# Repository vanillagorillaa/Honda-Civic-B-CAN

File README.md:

Honda B-CAN Integration
====

Get your panda deeper into your 2016+ Honda Civic, may work on other cars too, check Honda Techinfo for more details.

The Idea  
====

Access data found on a third CAN bus on your Honda Vehicle. Data on this bus includes Blind Spot Indicators (if vehicle equipped), lights, climate controls, and more.

Installation
====

This is a two part setup.

- Gateway - The Gateway contains a comma.ai panda [https://github.com/commaai/panda]. It has three CAN busses and uses the panda firmware to proxy the CAN messages from one bus to the other. Currently we are taking all messages from the BCAN (150kbps) and forwarding them onto the FCAN (500kbps). This will allow devices such as the comma two [https://comma.ai/shop/products/comma-two-devkit] and openpilot [https://github.com/commaai/openpilot] to see these new messages, and in the future, control. The gateway has six ethernet ports. Each ethernet port is labeled with its functionality as each is wired differently (see schematic for wiring). The gateway also has 0402 pads for terminating resistors on each bus (if needed). The Gateway is designed to be agnostic to vehicles. Simply follow the wiring to make your own compatible "Car Specific Board". Also includes a USB A for flashing the panda. 

1x - To Harness
1x - To OBDII Port/ comma power
1x - To pedal
2x - Car Specific board
1x - Expansion

- Honda B-CAN - This board has two JAE MX34036NF4 connectors and one Ethernet port. It is designed to connect to the 36 pin connector on the BCM of select Honda vehicles. The install procedure is so unplug the wiring harness from the BCM (confirmed on 2016 Honda Civic and 2017 Honda CRV, for more vehicles check Techinfo), connect it to the B-CAN board, then use the additional wiring harness (MX34036SF4 to MX34036SF4) to install between the B-CAN board and the BCM. Then use an ethernet cable to connect to the Gateway. This allows a full passthrough of the BCM harness, and taps into the BCAN and FCAN lines (to the Ethernet port). You can also sub the above JAE part numbers for another MX34036 series connector (just be sure to trim the connectors as seen in the build guide, otherwise the connector will not fit in the BCM)

====

Contributions welcome! Documentation can be greatly improved! Make a more detailed build guide!

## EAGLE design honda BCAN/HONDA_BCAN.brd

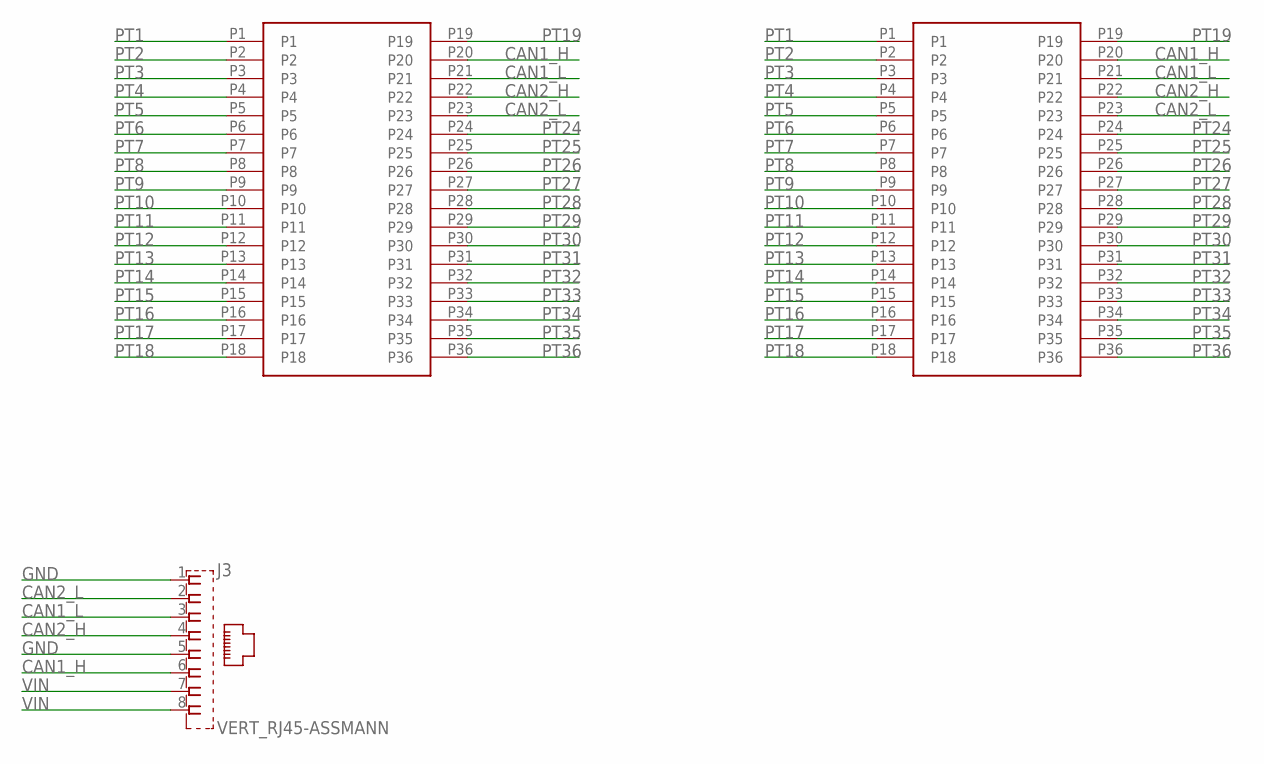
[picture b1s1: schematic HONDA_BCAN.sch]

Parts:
J1, J2: MX34036NF4; MPN MX34036NF4
J3: VERT_RJ45-ASSMANN; RJ45-VERT; MPN A-2004-2-4-LPS-N-R

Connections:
CAN1_H: J1.P20, J2.P20, J3.6
CAN1_L: J1.P21, J2.P21, J3.3
CAN2_H: J1.P22, J2.P22, J3.4
CAN2_L: J1.P23, J2.P23, J3.2
GND: J3.1, J3.5
PT1: J1.P1, J2.P1
PT2: J1.P2, J2.P2
PT3: J1.P3, J2.P3
PT4: J1.P4, J2.P4
PT5: J1.P5, J2.P5
PT6: J1.P6, J2.P6
PT7: J1.P7, J2.P7
PT8: J1.P8, J2.P8
PT9: J1.P9, J2.P9
PT10: J1.P10, J2.P10
PT11: J1.P11, J2.P11
PT12: J1.P12, J2.P12
PT13: J1.P13, J2.P13
PT14: J1.P14, J2.P14
PT15: J1.P15, J2.P15
PT16: J1.P16, J2.P16
PT17: J1.P17, J2.P17
PT18: J1.P18, J2.P18
PT19: J1.P19, J2.P19
PT24: J1.P24, J2.P24
PT25: J1.P25, J2.P25
PT26: J1.P26, J2.P26
PT27: J1.P27, J2.P27
PT28: J1.P28, J2.P28
PT29: J1.P29, J2.P29
PT30: J1.P30, J2.P30
PT31: J1.P31, J2.P31
PT32: J1.P32, J2.P32
PT33: J1.P33, J2.P33
PT34: J1.P34, J2.P34
PT35: J1.P35, J2.P35
PT36: J1.P36, J2.P36
VIN: J3.7, J3.8

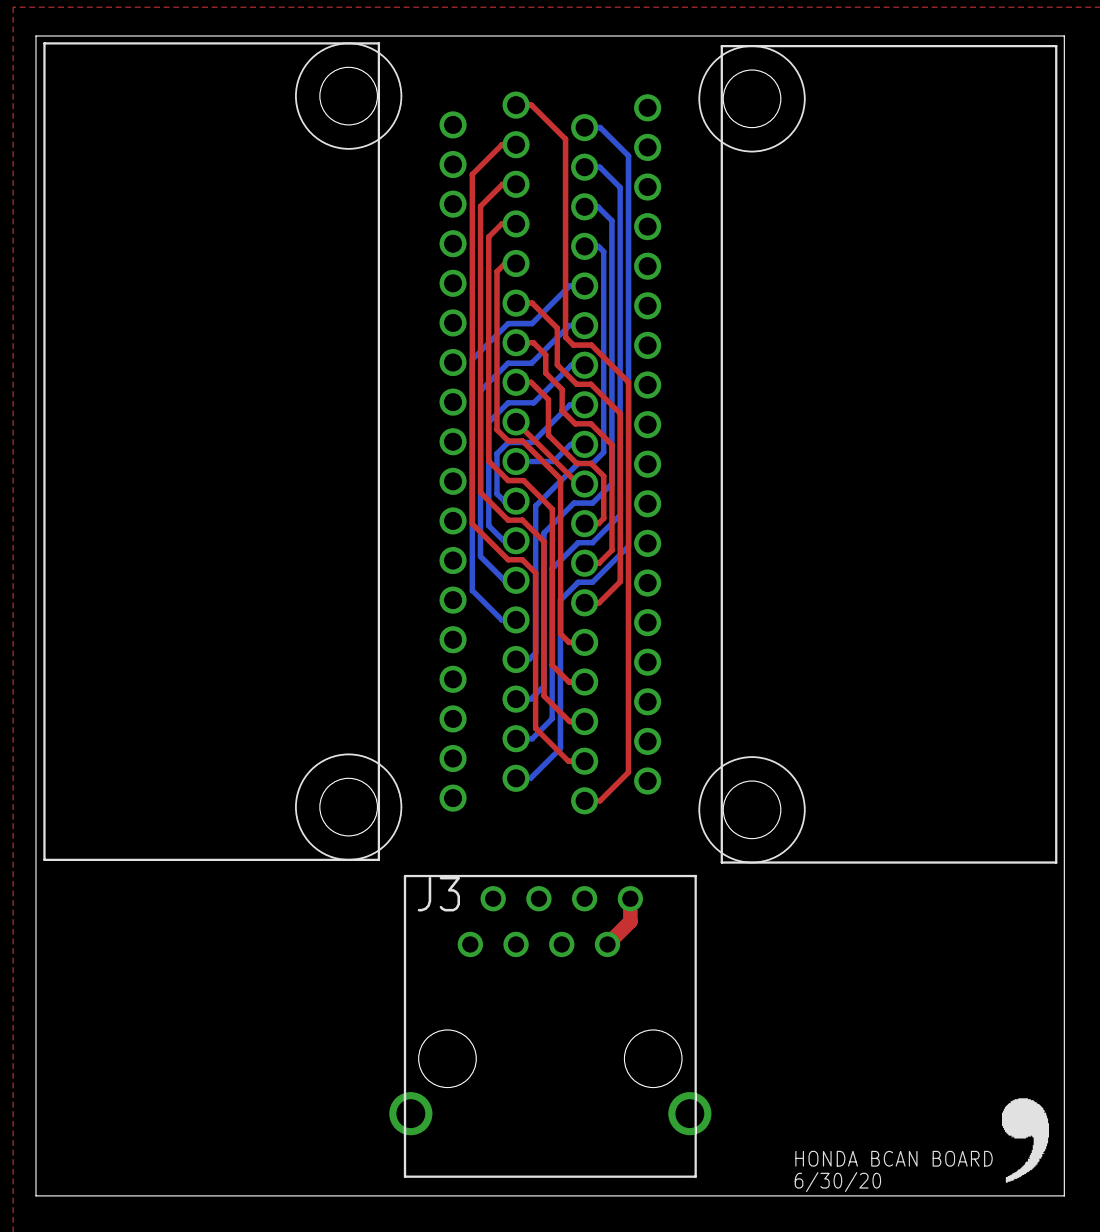
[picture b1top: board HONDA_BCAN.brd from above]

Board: 4 copper layers, 57.1 x 64.4 mm, 4 parts (0 on the bottom side), 38 nets.

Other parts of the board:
U$1: LOGO

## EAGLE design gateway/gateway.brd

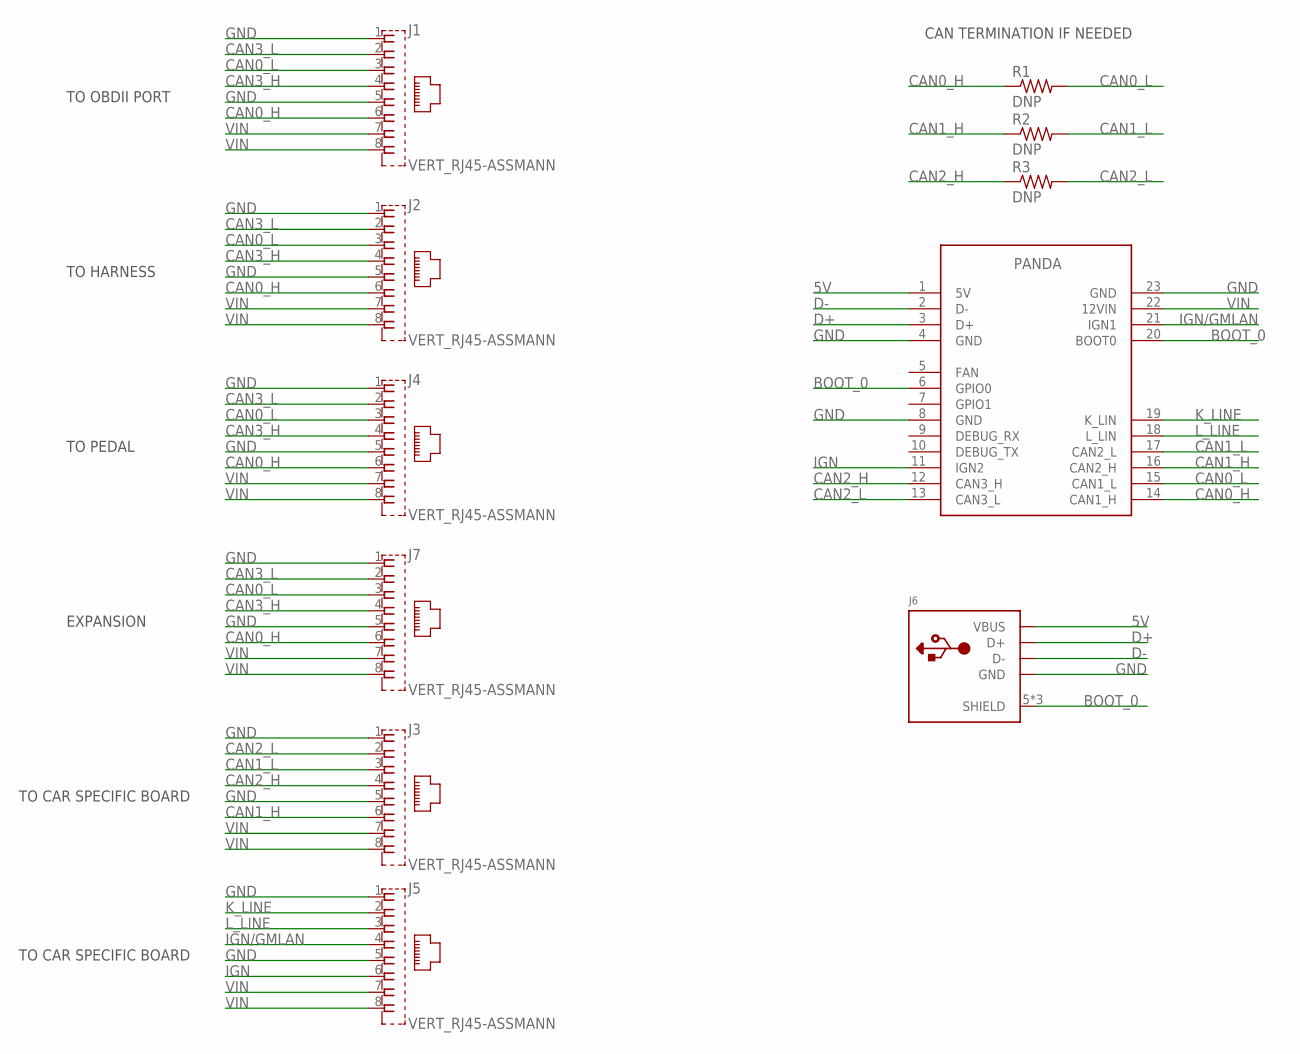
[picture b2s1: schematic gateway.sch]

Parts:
J1, J2, J3, J4, J5, J7: VERT_RJ45-ASSMANN; RJ45-VERT; MPN A-2004-2-4-LPS-N-R
J6: USB-AMOLEX; USB-A-VERT-MOLEX; MPN 1050570001
R1, R2, R3: DNP; 0603-R
U$1: PANDA; PANDA-FOOT

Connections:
5V: J6.1 (VBUS), U$1.1 (5V)
BOOT_0: J6.5 (SHIELD), J6.6 (SHIELD), J6.7 (SHIELD), U$1.6 (GPIO0), U$1.20 (BOOT0)
CAN0_H: J1.6, J2.6, J4.6, J7.6, R1.1, U$1.14 (CAN1_H)
CAN0_L: J1.3, J2.3, J4.3, J7.3, R1.2, U$1.15 (CAN1_L)
CAN1_H: J3.6, R2.1, U$1.16 (CAN2_H)
CAN1_L: J3.3, R2.2, U$1.17 (CAN2_L)
CAN2_H: J3.4, R3.1, U$1.12 (CAN3_H)
CAN2_L: J3.2, R3.2, U$1.13 (CAN3_L)
CAN3_H: J1.4, J2.4, J4.4, J7.4
CAN3_L: J1.2, J2.2, J4.2, J7.2
D+: J6.3 (D+), U$1.3 (D+)
D-: J6.2 (D-), U$1.2 (D-)
GND: J1.1, J1.5, J2.1, J2.5, J3.1, J3.5, J4.1, J4.5, J5.1, J5.5, J6.4 (GND), J7.1, J7.5, U$1.4 (GND), U$1.8 (GND), U$1.23 (GND)
IGN: J5.6, U$1.11 (IGN2)
IGN/GMLAN: J5.4, U$1.21 (IGN1)
K_LINE: J5.2, U$1.19 (K_LIN)
L_LINE: J5.3, U$1.18 (L_LIN)
VIN: J1.7, J1.8, J2.7, J2.8, J3.7, J3.8, J4.7, J4.8, J5.7, J5.8, J7.7, J7.8, U$1.22 (12VIN)

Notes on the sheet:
TO OBDII PORT
TO HARNESS
TO PEDAL
TO CAR SPECIFIC BOARD
EXPANSION
CAN TERMINATION IF NEEDED

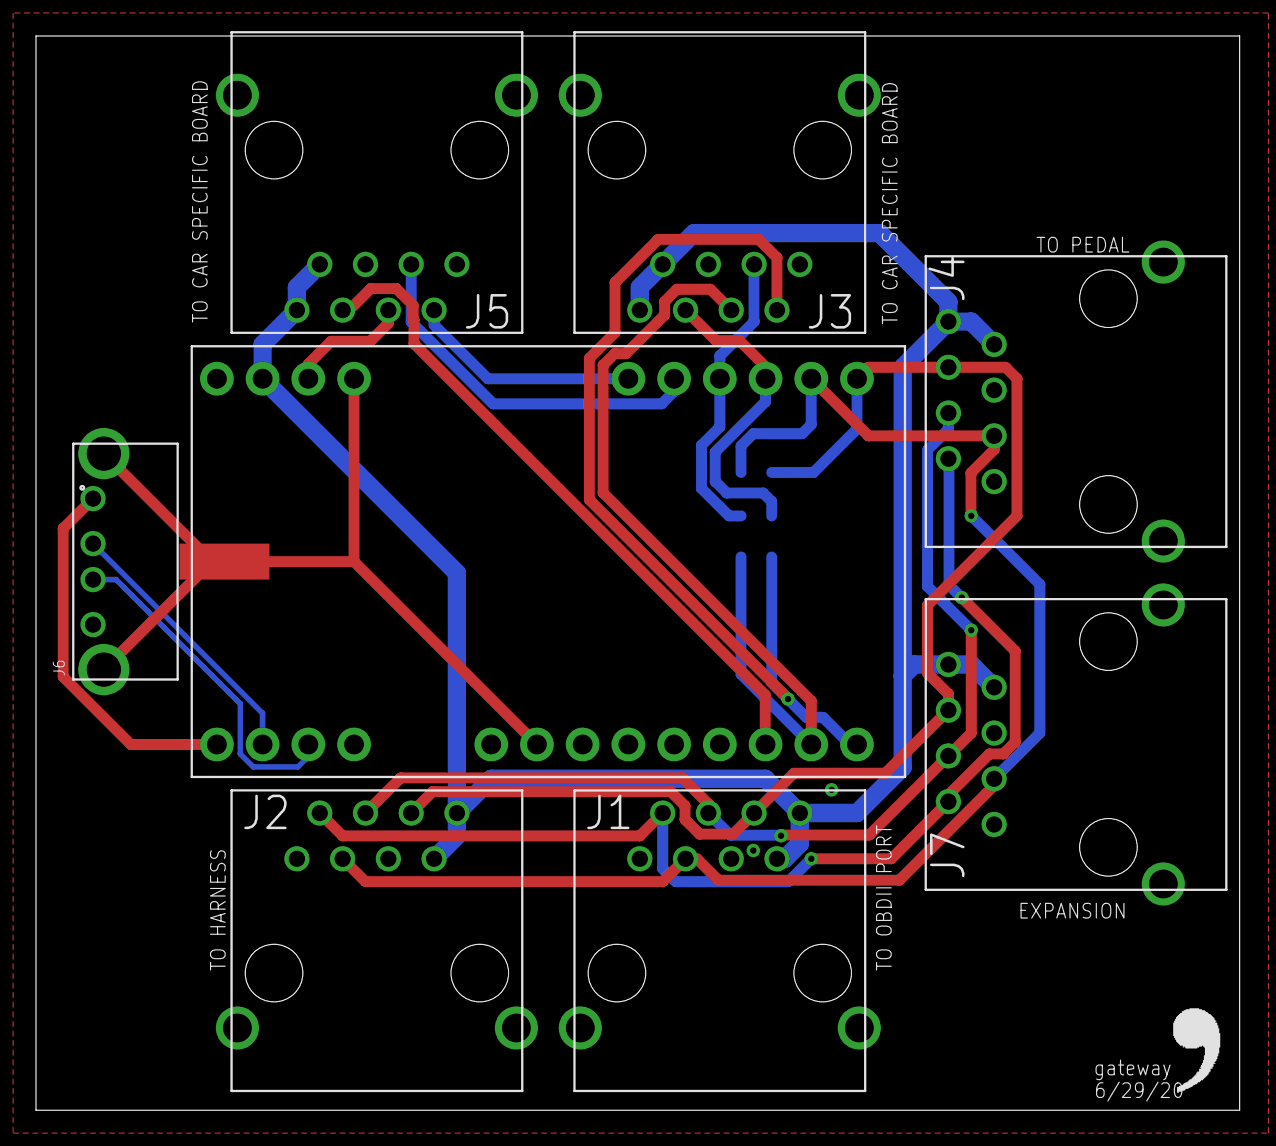
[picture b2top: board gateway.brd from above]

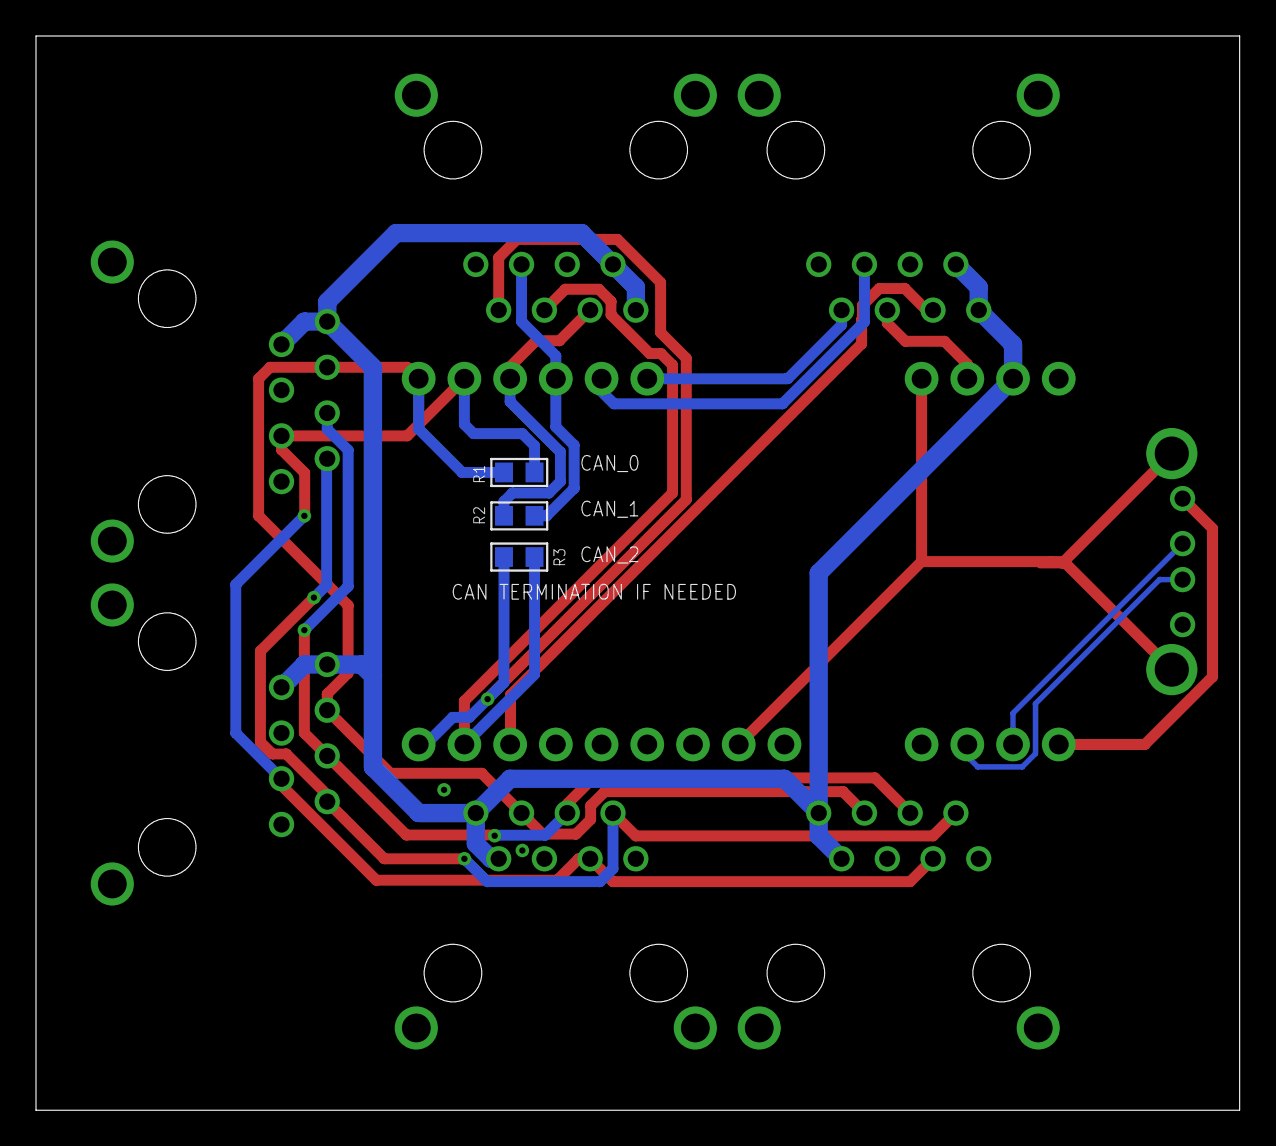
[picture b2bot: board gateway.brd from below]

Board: 2 copper layers, 66.9 x 59.7 mm, 12 parts (3 on the bottom side), 18 nets.

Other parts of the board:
U$2: LOGO

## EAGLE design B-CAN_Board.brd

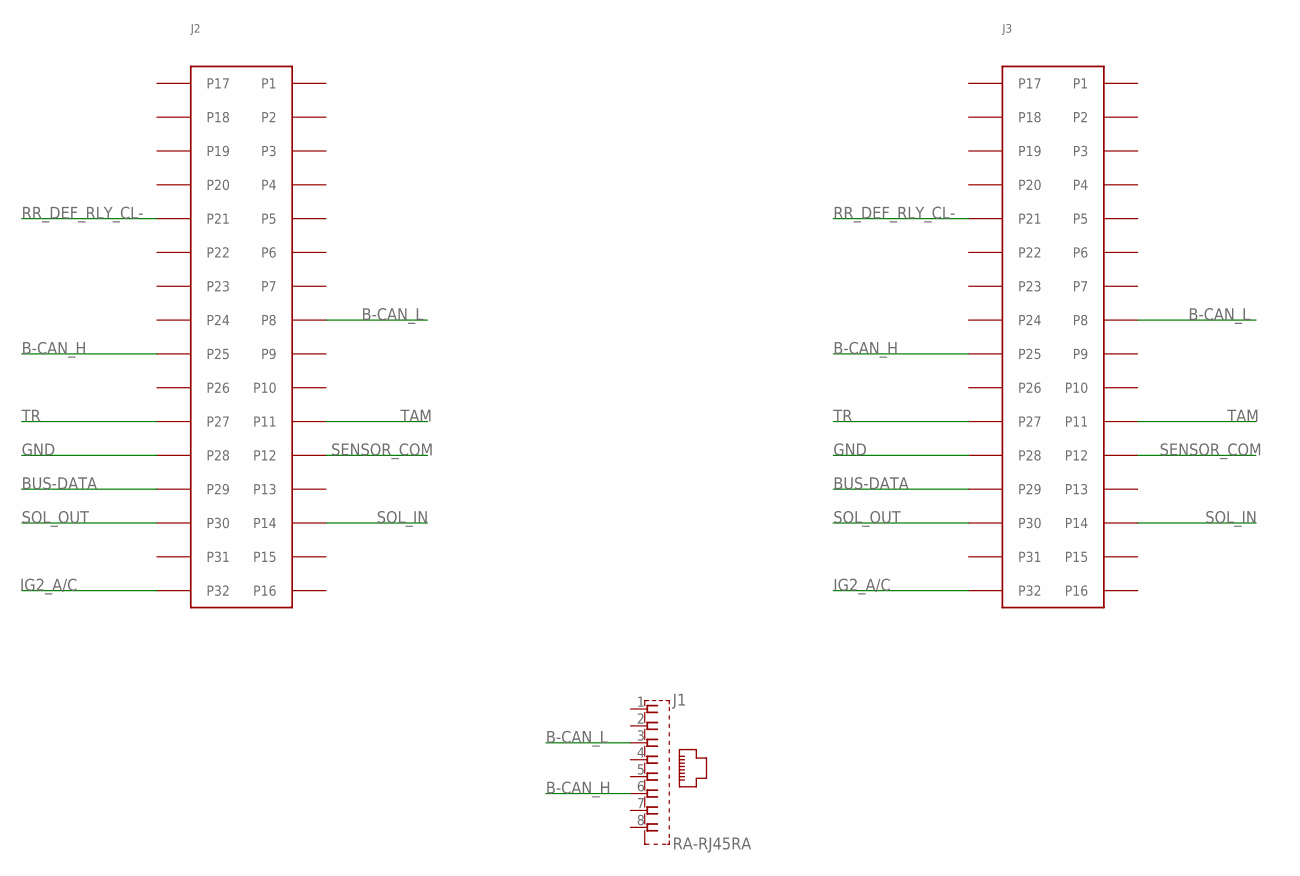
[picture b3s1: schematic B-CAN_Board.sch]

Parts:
J1: RA-RJ45RA; RA-RJ45
J2, J3: MX34032UF2

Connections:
B-CAN_H: J1.6, J2.P25, J3.P25
B-CAN_L: J1.3, J2.P8, J3.P8
BUS-DATA: J2.P29, J3.P29
GND: J2.P28, J3.P28
IG2_A/C: J2.P32, J3.P32
RR_DEF_RLY_CL-: J2.P21, J3.P21
SENSOR_COM: J2.P12, J3.P12
SOL_IN: J2.P14, J3.P14
SOL_OUT: J2.P30, J3.P30
TAM: J2.P11, J3.P11
TR: J2.P27, J3.P27

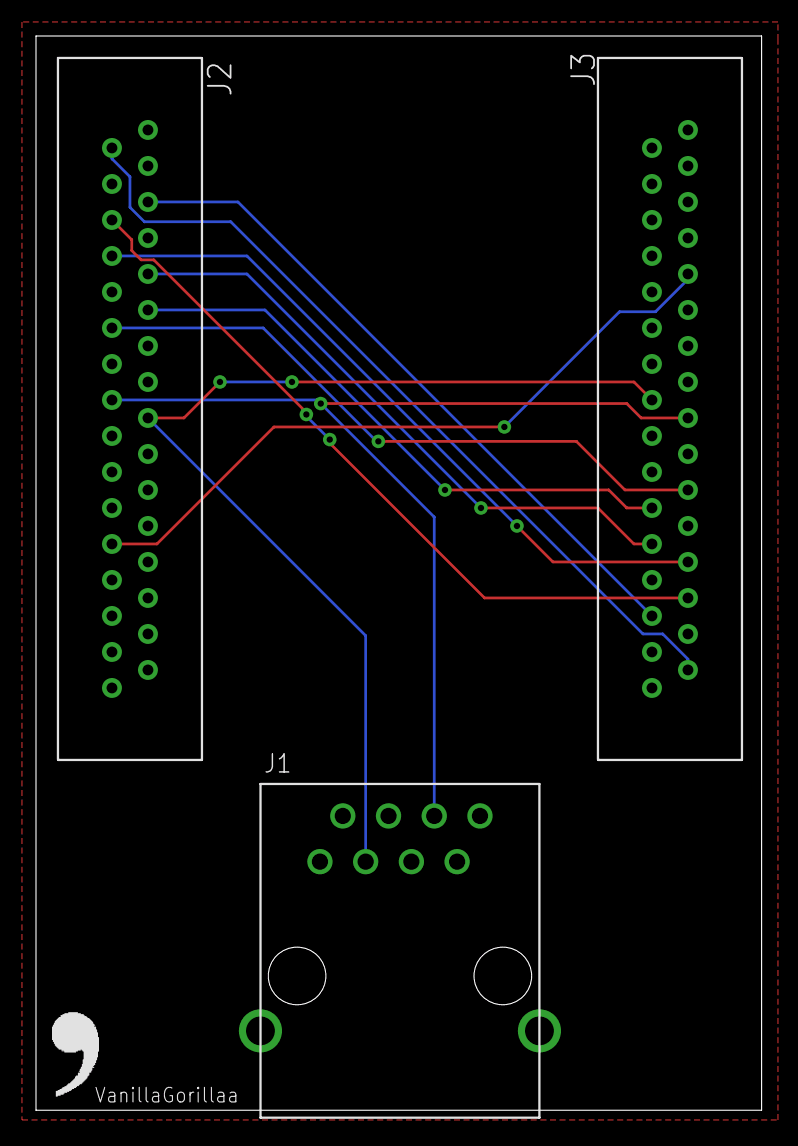
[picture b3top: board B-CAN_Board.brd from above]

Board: 2 copper layers, 40.3 x 59.7 mm, 4 parts (0 on the bottom side), 11 nets.

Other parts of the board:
U$2: LOGO

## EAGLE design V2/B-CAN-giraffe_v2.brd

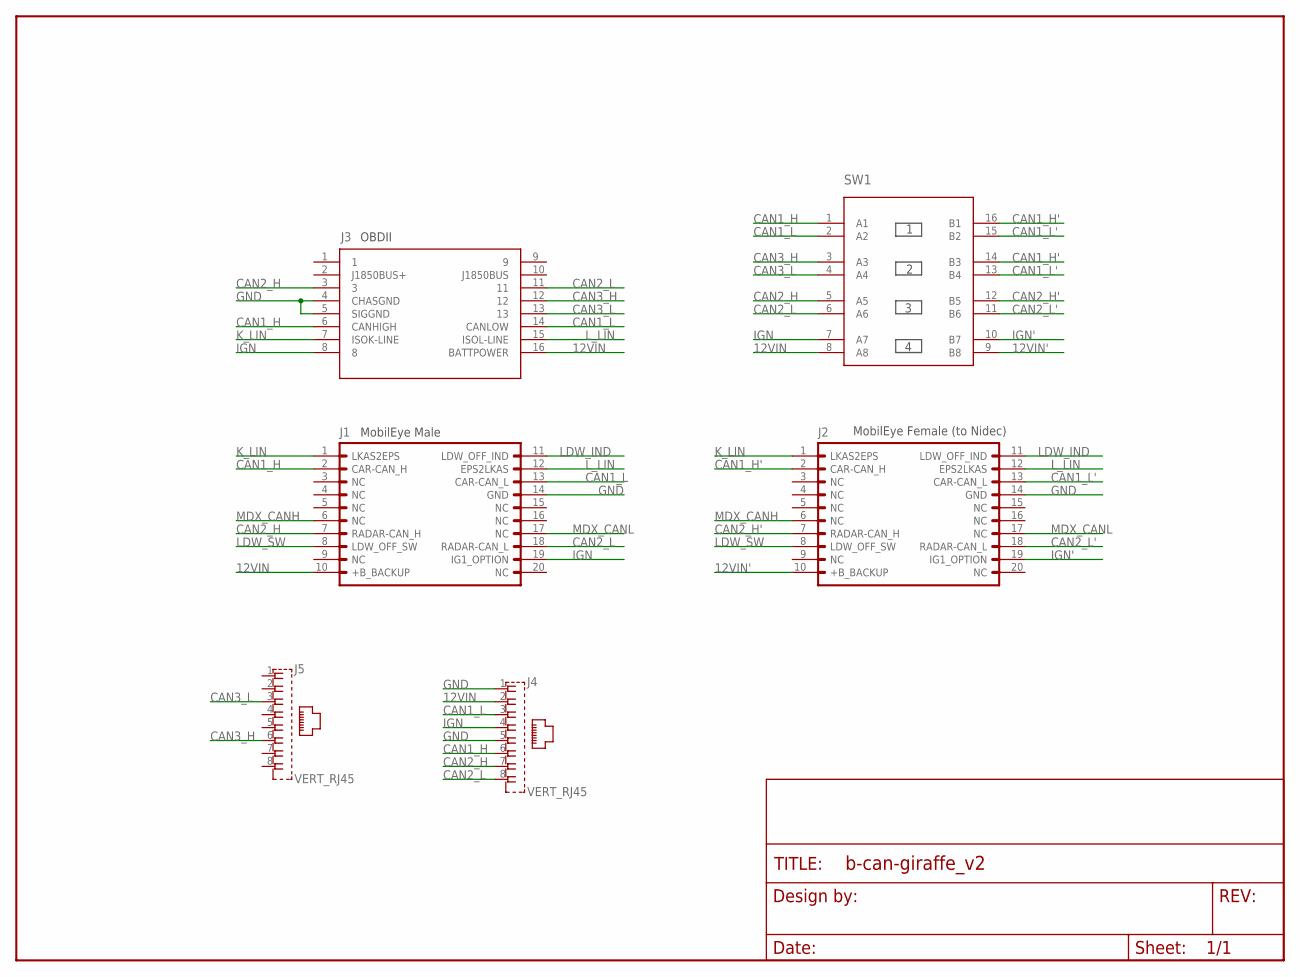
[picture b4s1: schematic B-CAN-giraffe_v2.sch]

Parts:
FRAME1: FRAME-LETTERNO_PACKAGE; DUMMY
J1: MOBILEYERAMALE; 2X10(RA)
J2: MOBILEYEFEMALE; 2X10(JAE_FEMALE)
J3: OBDII-FEMALE-CUT; OBDII-FEMALE-MIDCUT
J4, J5: VERT_RJ45; GLX-S-88M
SW1: 4XDPSTSMT; 4-DPST

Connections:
12VIN: J1.10 (+B_BACKUP), J3.16 (BATTPOWER), J4.2, SW1.8 (A8)
12VIN': J2.10 (+B_BACKUP), SW1.9 (B8)
CAN1_H: J1.2 (CAR-CAN_H), J3.6 (CANHIGH), J4.6, SW1.1 (A1)
CAN1_H': J2.2 (CAR-CAN_H), SW1.14 (B3), SW1.16 (B1)
CAN1_L: J1.13 (CAR-CAN_L), J3.14 (CANLOW), J4.3, SW1.2 (A2)
CAN1_L': J2.13 (CAR-CAN_L), SW1.13 (B4), SW1.15 (B2)
CAN2_H: J1.7 (RADAR-CAN_H), J3.3, J4.7, SW1.5 (A5)
CAN2_H': J2.7 (RADAR-CAN_H), SW1.12 (B5)
CAN2_L: J1.18 (RADAR-CAN_L), J3.11, J4.8, SW1.6 (A6)
CAN2_L': J2.18 (RADAR-CAN_L), SW1.11 (B6)
CAN3_H: J3.12, J5.6, SW1.3 (A3)
CAN3_L: J3.13, J5.3, SW1.4 (A4)
GND: J1.14 (GND), J2.14 (GND), J3.4 (CHASGND), J3.5 (SIGGND), J4.1, J4.5
IGN: J1.19 (IG1_OPTION), J3.8, J4.4, SW1.7 (A7)
IGN': J2.19 (IG1_OPTION), SW1.10 (B7)
K_LIN: J1.1 (LKAS2EPS), J2.1 (LKAS2EPS), J3.7 (ISOK-LINE)
LDW_IND: J1.11 (LDW_OFF_IND), J2.11 (LDW_OFF_IND)
LDW_SW: J1.8 (LDW_OFF_SW), J2.8 (LDW_OFF_SW)
L_LIN: J1.12 (EPS2LKAS), J2.12 (EPS2LKAS), J3.15 (ISOL-LINE)
MDX_CANH: J1.6 (NC), J2.6 (NC)
MDX_CANL: J1.17 (NC), J2.17 (NC)

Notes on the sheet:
OBDII
MobilEye Male
MobilEye Female (to Nidec)

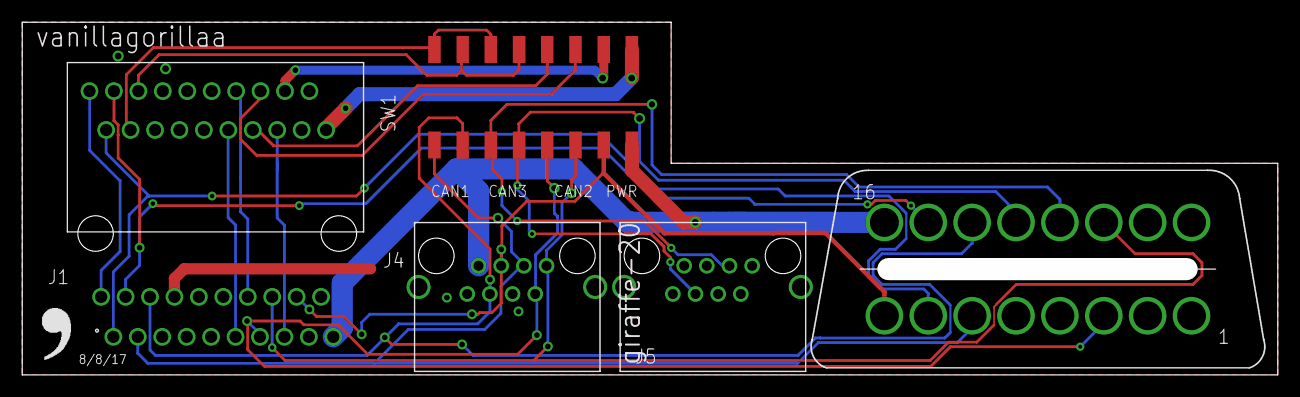
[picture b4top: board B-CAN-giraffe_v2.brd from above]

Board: 2 copper layers, 113.0 x 31.8 mm, 8 parts (1 on the bottom side), 21 nets.

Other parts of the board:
U$1: LOGO

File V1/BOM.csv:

Ref Des,Package,Manufacturer PN,Qty,Link
J1,20-pin-RA,MX34020NF1,1,https://www.digikey.com/product-detail/en/jae-electronics/MX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
J2,20-pin,MX34020SF1,1,https://www.digikey.com/scripts/DkSearch/dksus.dll?Detail&it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
,,M34S75C4F1,42,https://www.digikey.com/product-detail/en/jae-electronics/M3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
,,PRPC040SAAN-RC,1,https://www.digikey.com/products/en?keywords=S1011EC-40-ND
J3,16-pin,OBDII-FEMALE,1,https://cn1514770021qfbj.en.alibaba.com/product/60598699808-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
J4,RJ45-VERT,A-2014-2-4-LP/FS-R,1,https://www.digikey.com/scripts/DkSearch/dksus.dll?Detail&it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
SW1,SMD,204-214ST,1,https://www.digikey.com/scripts/DkSearch/dksus.dll?Detail&it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
SCREWs,Phillips,92010A118,2,https://www.mcmaster.com/#catalog/92010A118
U$1,CONN SOCKET 32POS HOUSING 2.2MM,MX34032UF2,1,https://www.digikey.com/product-detail/en/jae-electronics/MX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
U$2,CONN SOCKET 32POS HOUSING 2.2MM,1,MX34032SF1,https://www.digikey.com/product-detail/en/jae-electronics/MX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
X1,RJ45-VERT,A-2014-2-4-LP/FS-R,1,https://www.digikey.com/scripts/DkSearch/dksus.dll?Detail&it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

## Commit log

2018-08-08 Initial Commit of Honda Civic B-CAN boards
2018-08-19 Push V2 and organize into folders
2018-08-19 Fix Readme
2018-12-01 God this used to look so ugly, lets make it nice
2020-12-20 Commit of working Gateway and BCAN

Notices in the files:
parts and their libraries:
SparkFun-Aesthetics: Licensing: Creative Commons ShareAlike 4.0 International - https://creativecommons.org/licenses/by-sa/4.0
SparkFun-Aesthetics: Released under the Creative Commons Attribution Share-Alike 4.0 License
SparkFun-Aesthetics: https://creativecommons.org/licenses/by-sa/4.0
